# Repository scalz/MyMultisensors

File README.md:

# MyMultisensors

MyMultisensors is a compact multi sensors capable node for your/my home automation.
Optmized for very low power, ambiant sensors node, battery powered and wireless, i can easily add in each room. 

I have to say, this is one of my favorite board! well, you think i'm biased :) a bit true ;)
But the truth is i've never seen the same board before (with my requirements) or i wouldn't have made it!

I put multiple "constraints" on myself to get the best of what i can do myself imho.
- Most common sensors used indoor : Temperature/Humidity/Motion/Ambiant Light/Door Contact. Using the best low power sensors i know.
- Entry level MCU so noobs can easily play with it (well known 328p)
- Tiny so i can reuse the board if i need a simple motion or door contact device. One pcb allows multiple devices. Standardisation of main ambiant indoor devices with box.
- Thin, like a simple temperature/humidity tag. So coincell 2032. Depending on the scenario, I need to be able to change the battery holder for CR2032/CR2450/AAA.
- Very very low power. 2years min with a simple good brand CR2032 (depending of usecase). Choosing the right parts for low power.
- Mysensors Wireless programming and Signing/Authentication features are mandatory for a device which can do some security tasks like Motion detection.
- RFM69 and its nice range even with the low power RFM69CW version onboard. I'm finalizing the nrf24 version because it's a nice board, that would be too bad for nrf24 user ;)
- I also tried to take care of the routing; and to have strong, unbroken GND plane as it is very important to get best range, especially with monopole wire I'm using (it's also possible to use a planar pcb ant though) 
- and not the least constraint! I've tried to keep cost reasonable regarding if i would buy it, or people etc..

As everything is customizable, the choice of the battery or the custom pcb size (compact), the easy and quite common way is printing a custom box..

I think i've "almost" achieved my goals :)

We can see this is possible to use different kind of battery, and different antennas (wire or planar pcb).

### General specs
------

|Specs|  |
|---|---|
|Size |49*25.4 (mm) |
| MCU | Atmel328p TQFP 150nA deep sleep|
| Radio | RFM69CW 100nA in deep sleep, NRF24 is coming |
| Authentication security | ATSHA204A chip footprint 150nA in deep sleep|
| OverTheAir Wireless programming | SPI flash eeprom footprint 200nA in deep sleep |
| Temperature/Humidity | SI7021 60nA in deep sleep |
| Ambiant Light Lux | OPT3001 300nA in deep sleep, with footprint for optional pullup resistor |
| Motion detection | LHI968 good quality/price, with its circuit, active 1.6uA |
| Door contact | footprint for soldering an optional pullup resistor >1M | 
| Indicator Led | Yes, on D9 |
| Extension connector | FTDI + D3 for connecting Door contact | 
| Pogo pins | AVRSPI programming |
| Battery connectors | CR2032 240mAh, CR2450 500mAh, 2xAAA 1200mAh |
| Power Supply | Reverse-polarity protection. 3V3 max |

#### Onboard safety

Onboard, there is a reverse polarity protection. But for power savings, better efficiency etc .. there is no voltage regulator. So it's possible to use others batteries, or ftdi of course, but the max input voltage is 3.3V max.

#### Extension Connectors

For simplicity, and trying to boost my assembling process (i use reflow), i'm using pogopins. I've done a simple adapter like this..
- AVRSPI : for burning the bootloader. Here i'm using the Sensebender Micro Atmel 328p Internal 8Mhz BOD 1.8V, in Boards Manager/Mysensors boards
- FTDI : for uploading the sketch. Without an optimized sketch, no big power savings. it's hw/sw.. still work in progress, i'll never be happy :)

#### Power consumption, what can we expect ?

Power consumption has been checked with uCurrent Gold + old voltcraft vc506..

Measurement done with PIR enabled, sensors sleeping but without spiflash ic nor Door contact

| Mode | Varta coincell CR2032 | Duracell 2xAAA |
|---|---|---|
|MCU in deep sleep, interrupt on change |4uA | 3uA|
|MCU in deep sleep, interrupt on change Wdt Enabled | 8uA | 11uA|
|MCU running 1Mhz | 732uA | 737uA|

Few simple maths because battery lifetime can change for multiple reasons (battery brand, internal resistance of coincell etc.). I won't explain everything here.

Still important to remember, is we can't expect to have the complete 240mAh of a coincell. Better bet on 200mAh, for a good quality coincell. For bad quality, it can be worse! Bad clone coincell can have only 50% of usable energy! Try clone and good brands, you will see what i mean ;) it's up to you if you want to spend your time to replace batteries :)

As RFM69 radio power consumption is low during sleep mode, no need to disable it, so it allows to use listenmode and wakeup from mcu from deep sleep for instance.

Say a power consumption of 5uA during sleep mode, the PIR is enabled of course, but not triggered (note it is possible to disable the PIR motion sensor to save power).
And our RFM69 needs 30mA during 40ms. Rough estimation!  it does not spend this whole 40ms transmitting of course! And with automatic RSSI and power level control, the radio can consumes less power in TX.
On other hand, it does not take in account the signing time if feature is used.

So 30mA for 40ms, say 10 motions detection/hour, give us a theoretical estimation of 2.33years.
Not so bad..but the node can last a lot more if the software is well optimized and flexible to let user to set dynamically during days, the sensibility and motion detection settings etc..

#### Arduino Pin description

|Arduino sketch define| Arduino Pin | description |
|---|---|---|
| MY_OTA_FLASH_SS | 8 | EEprom CS pin |
| ATSHA204_PIN | 17 | ATSHA204A SOT23 pin (for authentication) |
| PIR_INT_PINH  | 6 | PIR motion sensor pin H |
| PIR_INT_PINL | 7 | PIR motion sensor pin L |
| MYNODE_LED_PIN | 9 | Status led pin |
| REED_SWITCH_PIN | 3 | Reed switch pin interrupt on int1 D3 |
| AMBIANT_LIGHT_INT | A1  | Ambiant light sensor pin interrupt |

### Some ideas for the Mysensors sketch
------

|General Node settings | Default Settings | Notes|
|---|---|---|
| MY_NODE_NAME | MYS_MOTION| Node/sketch name|
|MY_DEBUG|1.0| General Level Mysensors Debug messages. Comment it to save memory!|
|MY_DEBUG_SKETCH|1.0|Sketch Level Debug messages. Comment it to save memory!|
|MY_NODE_ID|AUTO| AUTO or set a fixed ID|
|PARENT_NODE_ID|| Uncomment it and set your parent node id if needed|
|RELEASE |1.0| Sketch version|
|MY_BAUD_RATE|38400||
|isMetric |true| true/false|
|//atsha204Class sha204(sha204Pin);||Uncomment to enable signing|
|//MY_OTA_FIRMWARE_FEATURE||Uncomment to enable OTA wireless programming|
|MY_RFM69_NETWORKID|100| Uncomment and set your preferred network id|
|MY_RFM69_ATC_TARGET_RSSI_DBM|-80| Uncomment and set your preferred RSSI target|
|LIGHT_H_LIMIT|100|High Threshold for Ambiant light sensor|
|LIGHT_L_LIMIT|20|Low Threshold for Ambiant light sensor|
|LIGHT_TRANSMIT_THRESHOLD|50| Delta needed for updating Ambiant sensor to controller|
|HUMI_TRANSMIT_THRESHOLD|5|Delta needed for updating Humidity sensor to controller|
|TEMP_TRANSMIT_THRESHOLD|1|Delta needed for updating Temperature sensor to controller|
|FORCE_TRANSMIT_INTERVAL|10| Intervalle time between transmit update|
|BATTERY_USB| |Uncomment if using ftdi, for batt voltage reading|
|BATTERY_VARTA_2032| |Uncomment if using CR2032, for batt voltage reading|
|BATTERY_DURAC_2450| |Uncomment if using CR2450, for batt voltage reading|
|BATTERY_DURAC_IND_2AAA| |Uncomment if using 2xAAA, for batt voltage reading|

|MyPirHelper.h | Default Settings | Notes |
|---|---|---|
| PIR_SETTLE_TIME | 20000| in milliseconds/ better 30000. Waiting for PIR settling at node init|
| PIR_DEFAULT_PULSES | 8| Programmable pulse counter : 1... 255 pulses but for 255 pulses you'll need to dance for a nice motion :)|
| PIR_DEFAULT_WINDOWTIME | 1| Window time : 0 to 3.  Range: 8s... 16s.  Time in sec = 8 * (value+1)|
| PIR_DEFAULT_CANCELTIME | 2| Cancel Time : 0 to 10. Range: 8s... 80s.  Time = 8 * (value+1)|
| PIR_DEFAULT_BLINDTIME | 2| Blind Time  : 0 to 15. Range: 0s... 120s. Time = 8 * value|

All these infos can be found in the source files.

#### External Libraries needed
- Opt3001      : https://github.com/node-it/EnvironOne/blob/master/src/Opt3001.h
- SI7021       : from Marcus Sorensen <marcus@electron14.com> 

#### From the controller view

These are the CHILD_IDs used for sensors, or for dynamic settings.

|CHILD NODE ID/CMD | Default ID | Notes|
|---|---|---|
| CHILD_ID_PIR | 1|PIR sensor |
| CHILD_ID_PIR_EN | 2|Enable PIR |
| CHILD_ID_TEMP  | 3|Temperature sensor|
| CHILD_ID_HUM | 4|Humidity Child node ID|
| CHILD_ID_LIGHT  | 5|Ambiant light Child node ID|
| CHILD_ID_DOOR | 6|Door reed switch|
| CMID_FULL   | 10|Command from controller with all params below in one tx. below is for debug..|
| CMID_PULSES   | 11|Command from controller to set PIR number of pulse for windows time  |
| CMID_WINDOWTIME   | 12|Command from controller to set PIR window time  |
| CMID_BLINDTIME | 13|Command from controller to set PIR blind time|
| CMID_CANCELTIME | 14|Command from controller to set PIR cancel time|
| CMID_EN_LIGHT | 15|Command from controller to enable Light sensor threshold|
| CMID_LIGHT_MODE | 16|Command from controller to set Light sensor special mode (enable pir at certain light level only...)|
| CMID_LIGHT_H  | 17|Command from controller to set Light sensor high threshold |
| CMID_LIGHT_L | 18|Command from controller to set Light sensor low threshold |
| CMID_LIGHT_DELTA | 19|Command from controller to set difference of lux for update controller |
| CMID_TRANSMIT_INTERVAL | 20|Command from controller to set time between sensor updates|
| CMID_TH_DELTA | 21|Command from controller to set difference of temp/hum needed for update controller |
| CMID_EN_LED  | 22|Command from controller to set led|

### Known issues
------ 

### TODO
------
- improve sketch

### Donations
------

I'm trying to make opensource projects. I do this for free and sharing spirit. I don't do ads etc..
But if you think information here is worth of some money, or want to reward me, feel free to send any amount through paypal.

Or you can also order pcb here :
I will earn a little percentage that will allow me to order proto pcb and share more fun design.

Or pay me a protein smoothie if you see me! oh well, a beer is ok too :)

### Contributors
------
Always special thanks to:
- Mysensors Team for its great work
- Adafruit, Sparkfun, TI, Atmel etc.. for all educational infos they share

### Links, reference and license 
------
- https://www.openhardware.io/view/75/MyMultisensors
- http://www2.st.com/content/ccc/resource/technical/document/application_note/b8/84/29/41/21/00/44/41/DM00096551.pdf/files/DM00096551.pdf/jcr:content/translations/en.DM00096551.pdf
- http://www.ti.com/lit/ug/tiduau1a/tiduau1a.pdf

Copyright Scalz (2016). released under the CERN Open Hardware Licence v1.2

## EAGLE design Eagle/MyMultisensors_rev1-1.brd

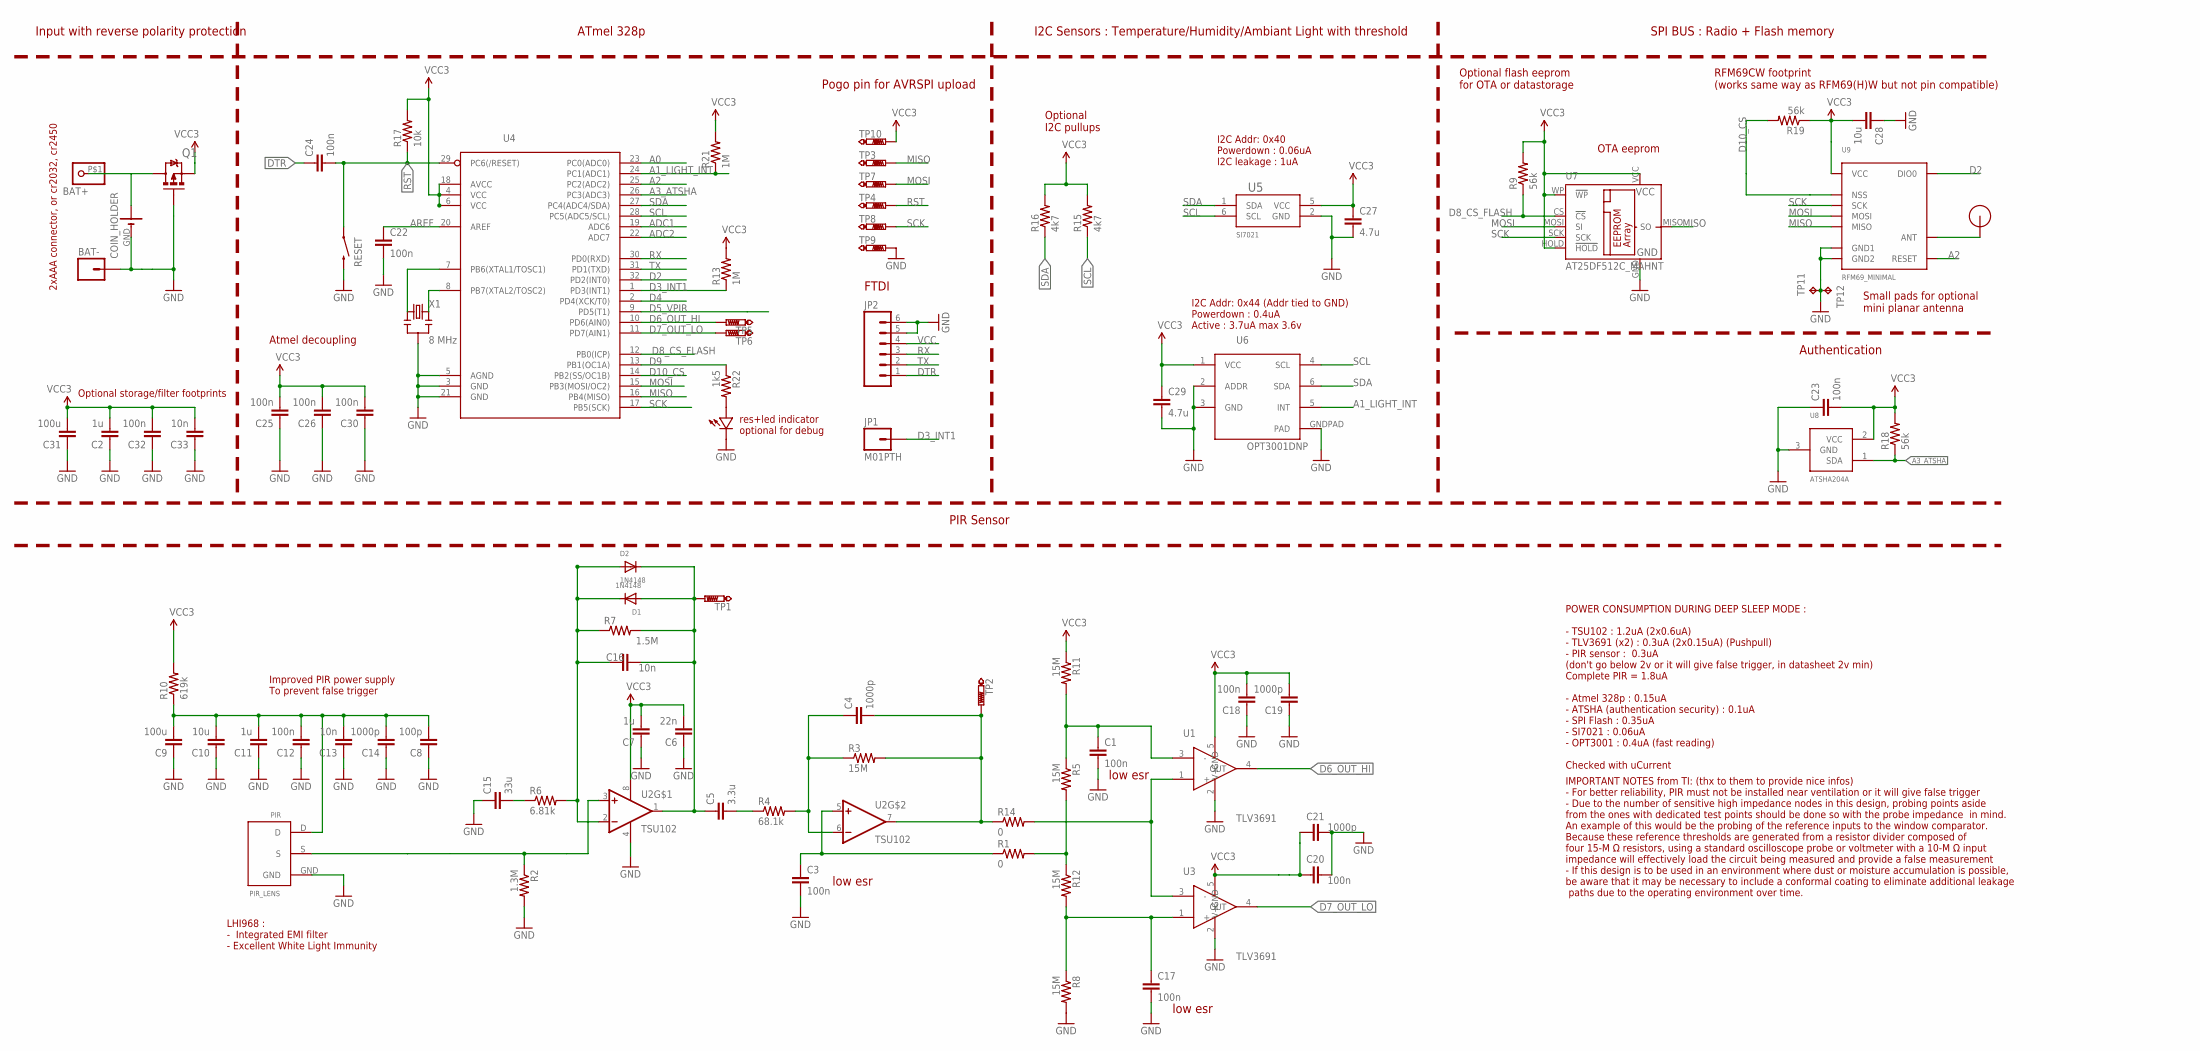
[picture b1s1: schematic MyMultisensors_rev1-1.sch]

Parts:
ANT: RFM12B_ANTENNA; RFM12B-ANTENNA
BAT+: PINHD-1X1TOP; 1X01_ONESIDE
BAT-: M01PTH; 1X01
C1, C3, C12, C17, C18, C20, C22, C23, C25, C26, C30, C32: 100n; 0603-CAP
C2: 1u; 0805-CAP
C4, C14, C19, C21: 1000p; 0603-CAP
C5: 3.3u; 0603-CAP
C6: 22n; 0603-CAP
C7, C11: 1u; 0603-CAP
C8: 100p; 0603-CAP
C9, C31: 100u; 0805-CAP
C10, C28: 10u; 0805-CAP
C13, C16, C33: 10n; 0603-CAP
C15: 33u; 0805-CAP
C24: 100n; 0805-CAP
C27, C29: 4.7u; 0603-CAP
COIN_HOLDER: CR2450_H_LOWCOSTVERTICAL_WITH_MILL; CR2450H_LOWCOST2
D1, D2: 1N4148; SOD-123
D3: LED0805; 0805-LED
JP1: M01PTH; 1X01
JP2: M06SIP; 1X06
PIR: PIR_LENS
Q1: SI2399DS-T1-GE3; SOT95P237X112-3N
R1, R14: 0; 0603-RES
R2: 1.3M; 0603-RES
R3, R5, R8, R11, R12: 15M; 0603-RES
R4: 68.1k; 0603-RES
R6: 6.81k; 0603-RES
R7: 1.5M; 0603-RES
R9, R18, R19: 56k; 0603-RES
R10: 619k; 0603-RES
R13, R21: 1M; 0603-RES
R15, R16: 4k7; 0603-RES
R17: 10k; 0805-RES
R22: 1k5; 0603-RES
RESET: SWITCH-MOMENTARY-2-SMD-1101NE; TACTILE-SWITCH-1101NE
TP1, TP2, TP5, TP6: PTR1B1,27; B1,27
TP3, TP4, TP7, TP8, TP9, TP10: PTR1TP18R; TP18R
TP11, TP12: TPTP10SQ; TP10SQ
U1, U3: TLV3691; SC70-5
U2: TSU102; MINI_SO8
U4: ATMega-328; TQFP32-08
U5: SI7021; DFN6
U6: OPT3001DNP
U7: AT25DF512C_MAHNT
U8: ATSHA204A; SOT23
U9: RFM69_MINIMAL; RFM69CW_MINIMAL
X1: 8 MHz; RESONATOR-SMD

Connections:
A0: U4.23 (PC0(ADC0))
A1_LIGHT_INT: R21.1, U4.24 (PC1(ADC1)), U6.5 (INT)
A2: U4.25 (PC2(ADC2)), U9.RESET
A3_ATSHA: R18.1, U4.26 (PC3(ADC3)), U8.1 (SDA)
ADC1: U4.19 (ADC6)
ADC2: U4.22 (ADC7)
AREF: C22.1, U4.20 (AREF)
D2: U4.32 (PD2(INT0)), U9.DIO0
D3_INT1: JP1.1, R13.1, U4.1 (PD3(INT1))
D4: U4.2 (PD4(XCK/T0))
D5_VPIR: U4.9 (PD5(T1))
D6_OUT_HI: TP5.TP, U1.4 (OUT), U4.10 (PD6(AIN0))
D7_OUT_LO: TP6.TP, U3.4 (OUT), U4.11 (PD7(AIN1))
D8_CS_FLASH: R9.1, U4.12 (PB0(ICP)), U7.CS (!CS)
D9: R22.1, U4.13 (PB1(OC1A))
D10_CS: R19.2, U4.14 (PB2(SS/OC1B)), U9.NSS
DTR: C24.1, JP2.1
GND: BAT-.1, C1.2, C2.1, C3.2, C6.1, C7.1, C8.1, C9.1, C10.1, C11.1, C12.1, C13.1, C14.1, C15.1, C17.2, C18.1, C19.1, C20.1, C21.1, C22.2, C23.1, C25.1, C26.1, C27.2, C28.1, C29.2, C30.1, C31.1, C32.1, C33.1, COIN_HOLDER.GND (-), D3.MINUS, JP2.5, JP2.6, PIR.GND, Q1.1 (G), R2.2, R8.2, RESET.P$2 (2), TP9.TP, TP11.TP, TP12.TP, U1.2 (GND), U2.4 (V-), U3.2 (GND), U4.3 (GND), U4.5 (AGND), U4.21 (GND), U5.2 (GND), U6.2 (ADDR), U6.3 (GND), U6.GNDPAD (PAD), U7.GND, U8.3 (GND), U9.GND (GND1), U9.GND2, X1.2
MISO: TP3.TP, U4.16 (PB4(MISO)), U7.MISO (SO), U9.MISO
MOSI: TP7.TP, U4.15 (PB3(MOSI/OC2)), U7.MOSI (SI), U9.MOSI
unnamed: C17.1, R8.1, R12.2, U3.1 (+)
unnamed: PIR.S, R2.1, U2.3 (+IN)
unnamed: D3.PLUS, R22.2
unnamed: C16.1, D1.C, D2.A, R6.2, R7.1, U2.2 (-IN)
unnamed: C15.2, R6.1
unnamed: C5.1, C16.2, D1.A, D2.C, R7.2, TP1.TP, U2.1 (OUT)
unnamed: C5.2, R4.1
unnamed: C4.1, R3.1, R4.2, U2.6 (-IN)
unnamed: C4.2, R3.2, R14.1, TP2.TP, U2.7 (OUT)
unnamed: U4.7 (PB6(XTAL1/TOSC1)), X1.1
unnamed: C1.1, R5.1, R11.2, U1.3 (-)
unnamed: C3.1, R1.1, U2.5 (+IN)
unnamed: C8.2, C9.2, C10.2, C11.2, C12.2, C13.2, C14.2, PIR.D, R10.1
unnamed: R14.2, U1.1 (+), U3.3 (-)
unnamed: R1.2, R5.2, R12.1
unnamed: U4.8 (PB7(XTAL2/TOSC2)), X1.3
unnamed: ANT.P$1, U9.ANT
unnamed: BAT+.P$1, COIN_HOLDER.VBAT@1 (+), COIN_HOLDER.VBAT@2 (+), COIN_HOLDER.VBAT@3 (+), COIN_HOLDER.VBAT@4 (+), Q1.3 (D)
RST: C24.2, R17.1, RESET.P$1 (1), TP4.TP, U4.29 (PC6(/RESET))
RX: JP2.3, U4.30 (PD0(RXD))
SCK: TP8.TP, U4.17 (PB5(SCK)), U7.SCK, U9.SCK
SCL: R15.1, U4.28 (PC5(ADC5/SCL)), U5.6 (SCL), U6.4 (SCL)
SDA: R16.1, U4.27 (PC4(ADC4/SDA)), U5.1 (SDA), U6.6 (SDA)
TX: JP2.2, U4.31 (PD1(TXD))
VCC: C2.2, C6.2, C7.2, C18.2, C19.2, C20.2, C21.2, C23.2, C25.2, C26.2, C27.1, C28.2, C29.1, C30.2, C31.2, C32.2, C33.2, JP2.4, Q1.2 (S), R9.2, R10.2, R11.1, R13.2, R15.2, R16.2, R17.2, R18.2, R19.1, R21.2, TP10.TP, U1.5 (V+), U2.8 (V+), U3.5 (V+), U4.4 (VCC), U4.6 (VCC), U4.18 (AVCC), U5.5 (VCC), U6.1 (VCC), U7.HOLD (!HOLD), U7.VCC, U7.WP (!WP), U8.2 (VCC), U9.VDD (VCC)

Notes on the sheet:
IMPORTANT NOTES from TI: (thx to them to provide nice infos) - For better reliability, PIR must not be installed near ventilation or it will give false trigger - Due to the number of sensitive high impedance nodes in this design, probing points aside from the ones with dedicated test points should 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
POWER CONSUMPTION DURING DEEP SLEEP MODE : - TSU102 : 1.2uA (2x0.6uA) - TLV3691 (x2) : 0.3uA (2x0.15uA) (Pushpull) - PIR sensor : 0.3uA (don't go below 2v or it will give false trigger, in datasheet 2v min) Complete PIR = 1.8uA - Atmel 328p : 0.15uA - ATSHA (authentication security) : 0.1uA - SPI F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
LHI968 : - Integrated EMI filter - Excellent White Light Immunity
Optional I2C pullups
I2C Addr: 0x40 Powerdown : 0.06uA I2C leakage : 1uA
I2C Addr: 0x44 (Addr tied to GND) Powerdown : 0.4uA Active : 3.7uA max 3.6v
RFM69CW footprint (works same way as RFM69(H)W but not pin compatible)
Atmel decoupling
res+led indicator optional for debug
PIR Sensor
I2C Sensors : Temperature/Humidity/Ambiant Light with threshold
ATmel 328p
Input with reverse polarity protection
SPI BUS : Radio + Flash memory
Authentication
Optional storage/filter footprints
2xAAA connector, or cr2032, cr2450
Improved PIR power supply To prevent false trigger
low esr
OTA eeprom
Pogo pin for AVRSPI upload
FTDI
Small pads for optional mini planar antenna
Optional flash eeprom for OTA or datastorage

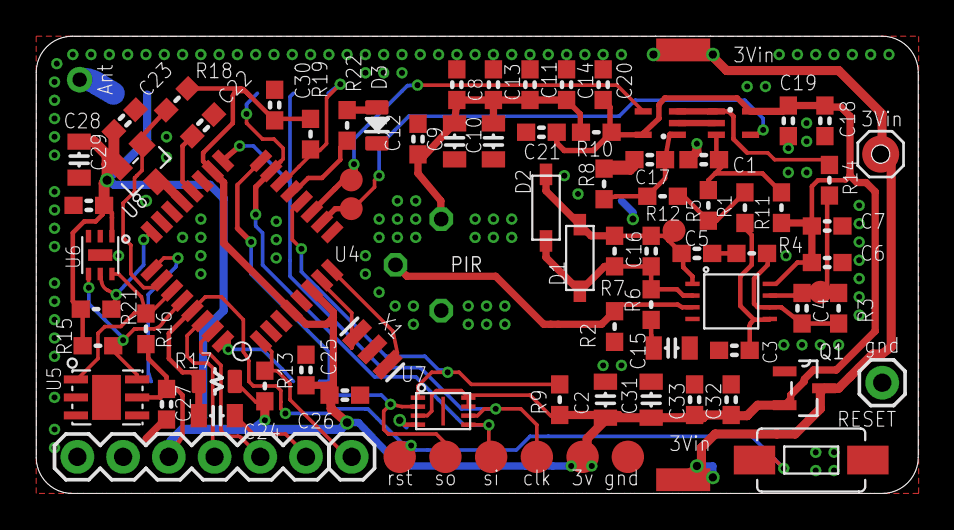
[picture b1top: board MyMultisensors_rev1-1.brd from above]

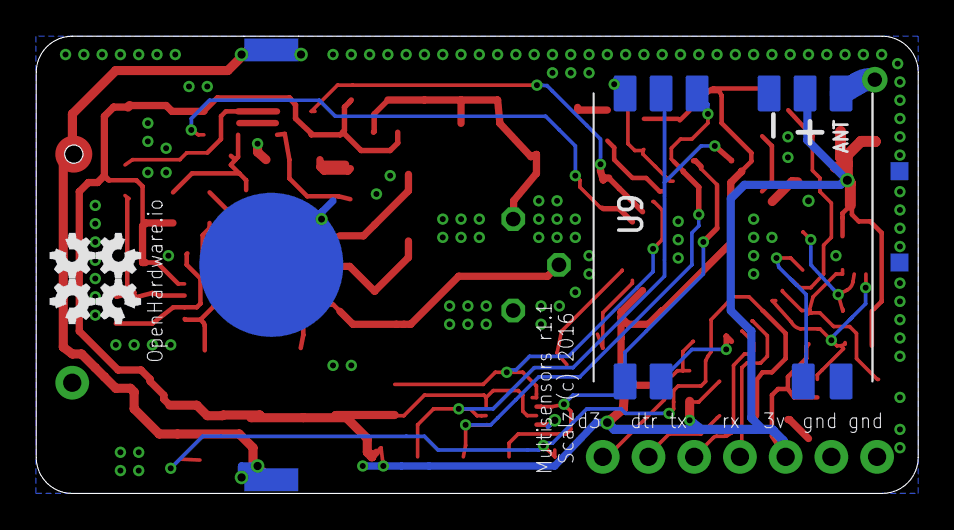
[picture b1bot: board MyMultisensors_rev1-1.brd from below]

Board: 2 copper layers, 49.0 x 25.4 mm, 89 parts (5 on the bottom side), 40 nets.

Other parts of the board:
U$6: OPENHW_IO_SMALL

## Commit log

2016-12-04 update description
2016-12-04 update desc and design files
2017-02-08 Reverse polarity protection fixed
    Drain and source was inverted on Q1 for revision 1.0 powering through
    mosfet diode (0.6V) when polarity was crossed.
2019-09-29 Fix Markdown style in README.md
    Fix headlines and tables

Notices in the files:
Eagle/MyMultisensors_rev1-1.brd:
Scalz (c) 2016
parts and their libraries:
SparkFun-Connectors: Licensing: Creative Commons ShareAlike 4.0 International - https://creativecommons.org/licenses/by-sa/4.0
